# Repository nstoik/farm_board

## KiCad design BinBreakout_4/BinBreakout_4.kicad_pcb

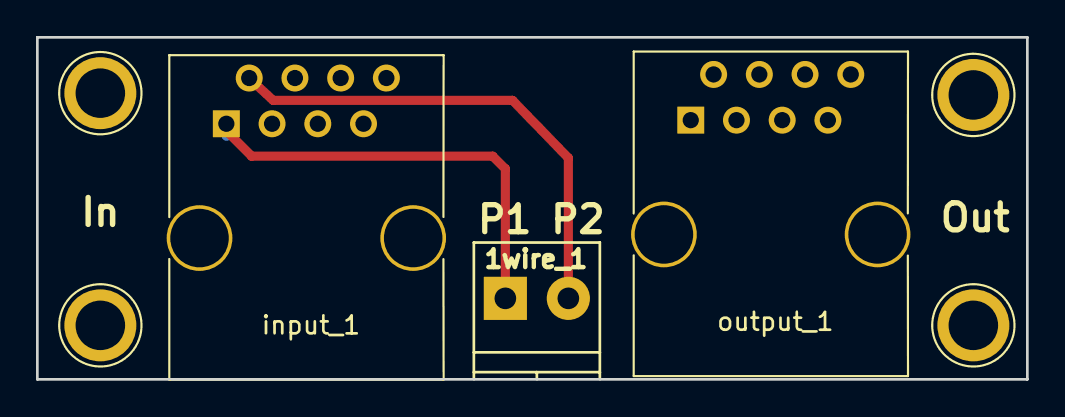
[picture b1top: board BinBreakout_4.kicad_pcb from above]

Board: 2 copper layers, 55.0 x 19.0 mm, 3 parts (0 on the bottom side), 2 nets.

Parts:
1wire_1: Screw_Terminal_01x02; TerminalBlock_Phoenix_PT-3.5mm_2pol
input_1: RJ45; RJ45_8
output_1: RJ45_8

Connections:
/pin_1: 1wire_1.1, input_1.1
/pin_2: 1wire_1.2, input_1.2

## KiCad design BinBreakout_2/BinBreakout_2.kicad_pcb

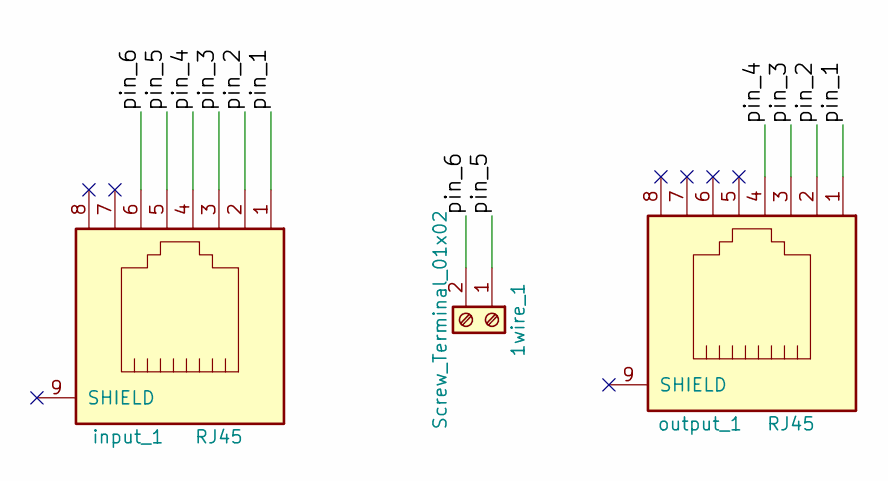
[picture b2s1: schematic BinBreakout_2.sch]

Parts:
1wire_1: Screw_Terminal_01x02; TerminalBlock_Phoenix_PT-3.5mm_2pol
input_1: RJ45; RJ45_8
output_1: RJ45; RJ45_8

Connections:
/pin_1: input_1.1, output_1.1
/pin_2: input_1.2, output_1.2
/pin_3: input_1.3, output_1.3
/pin_4: input_1.4, output_1.4
/pin_5: 1wire_1.1, input_1.5
/pin_6: 1wire_1.2, input_1.6

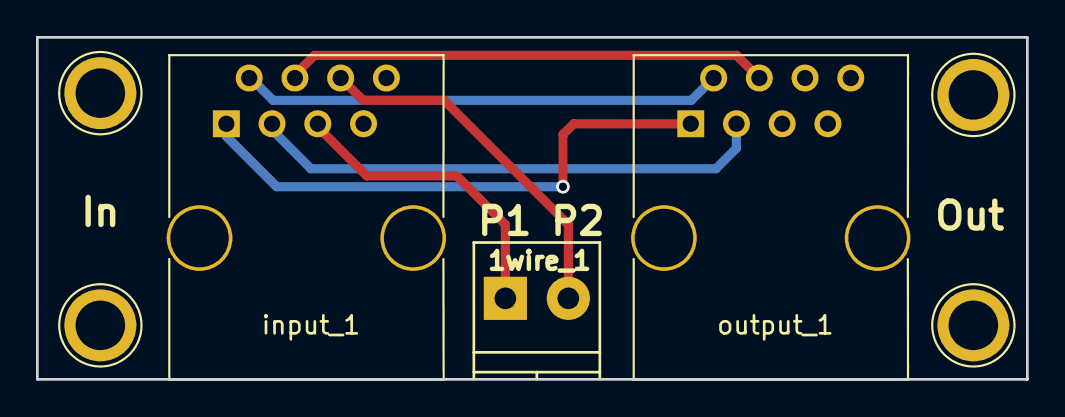
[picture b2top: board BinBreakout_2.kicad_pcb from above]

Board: 2 copper layers, 55.0 x 19.0 mm, 3 parts (0 on the bottom side), 6 nets.

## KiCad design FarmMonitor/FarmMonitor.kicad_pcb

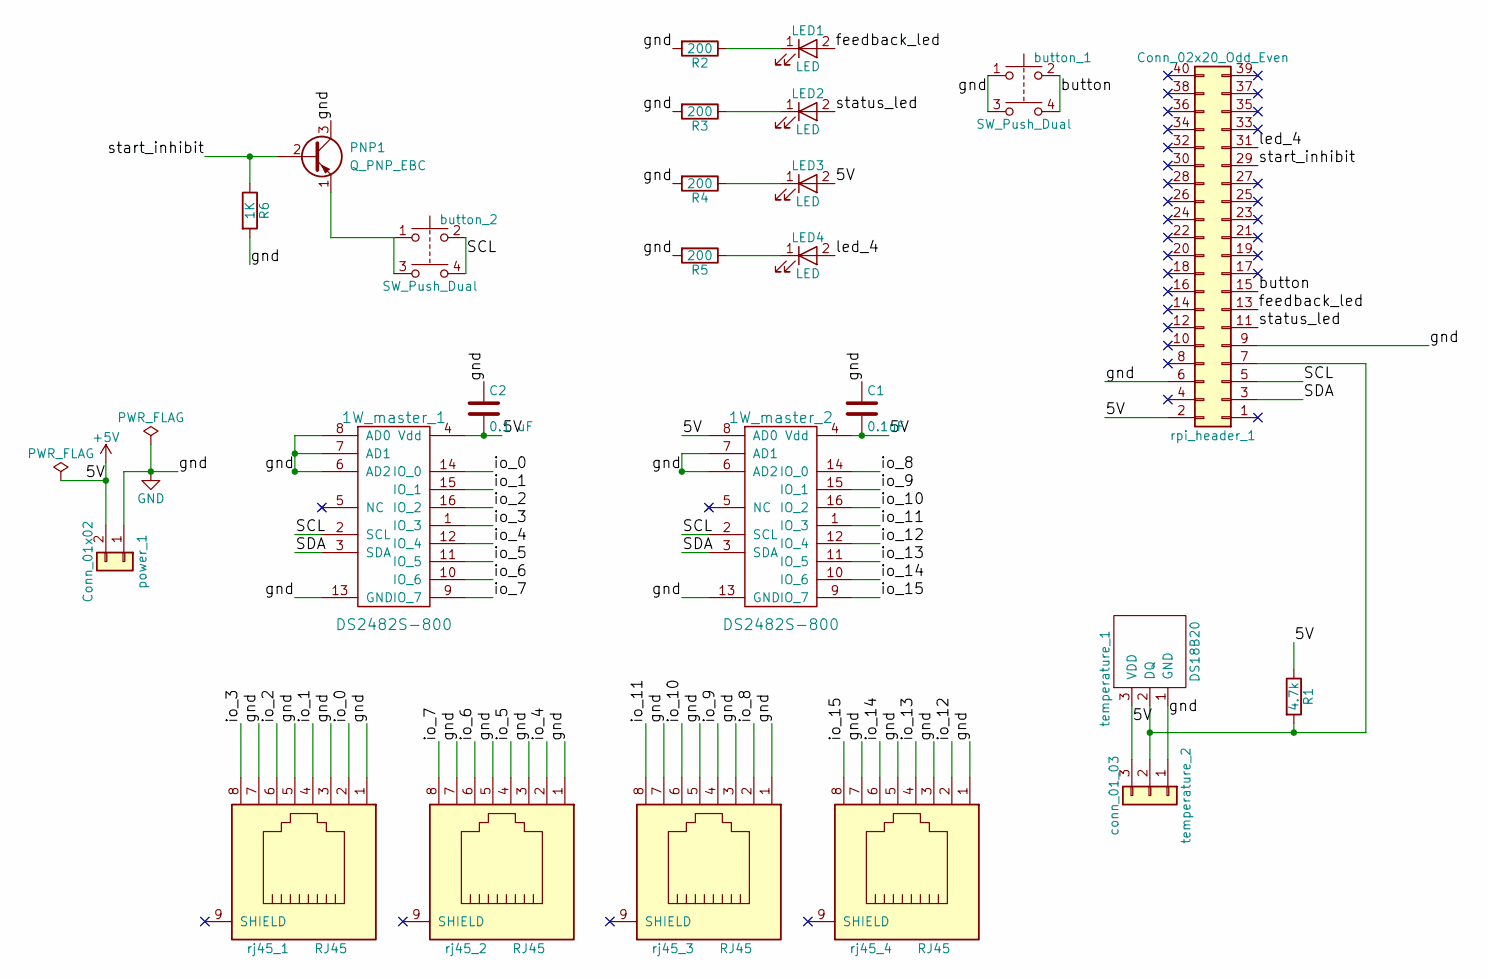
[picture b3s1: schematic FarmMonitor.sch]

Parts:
1W_master_1, 1W_master_2: DS2482S-800; SO-16-N
C1: 0.1uF; C_0805_HandSoldering
C2: 0.1 uF; C_0805_HandSoldering
LED1, LED2, LED3, LED4: LED; LED_D5.0mm
PNP1: Q_PNP_EBC; TO-92_Inline_Narrow_Oval
R1: 4.7k; R_0805_HandSoldering
R2, R3, R4, R5: 200; R_0805_HandSoldering
R6: 1K; R_0805_HandSoldering
button_1, button_2: SW_Push_Dual; Push_E-Switch_KS01Q01
power_1: Conn_01x02; TerminalBlock_Phoenix_PT-3.5mm_2pol
rj45_1, rj45_2, rj45_3, rj45_4: RJ45; RJ45_8
rpi_header_1: Conn_02x20_Odd_Even; Socket_Strip_Straight_2x20_Pitch2.54mm
temperature_1: DS18B20; TO-92_Horizontal2_Inline_Narrow_Oval
temperature_2: conn_01_03; TerminalBlock_Phoenix_MPT-2.54mm_3pol

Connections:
+5V: 1W_master_1.4 (Vdd), 1W_master_2.4 (Vdd), 1W_master_2.8 (AD0), C1.2, C2.2, LED3.2 (A), R1.1, power_1.2, rpi_header_1.2, temperature_1.3 (VDD), temperature_2.3
/SCL: 1W_master_1.2 (SCL), 1W_master_2.2 (SCL), button_2.2, button_2.4, rpi_header_1.5
/SDA: 1W_master_1.3 (SDA), 1W_master_2.3 (SDA), rpi_header_1.3
/button: button_1.2, button_1.4, rpi_header_1.15
/feedback_led: LED1.2 (A), rpi_header_1.13
/io_0: 1W_master_1.14 (IO_0), rj45_1.2
/io_1: 1W_master_1.15 (IO_1), rj45_1.4
/io_2: 1W_master_1.16 (IO_2), rj45_1.6
/io_3: 1W_master_1.1 (IO_3), rj45_1.8
/io_4: 1W_master_1.12 (IO_4), rj45_2.2
/io_5: 1W_master_1.11 (IO_5), rj45_2.4
/io_6: 1W_master_1.10 (IO_6), rj45_2.6
/io_7: 1W_master_1.9 (IO_7), rj45_2.8
/io_8: 1W_master_2.14 (IO_0), rj45_3.2
/io_9: 1W_master_2.15 (IO_1), rj45_3.4
/io_10: 1W_master_2.16 (IO_2), rj45_3.6
/io_11: 1W_master_2.1 (IO_3), rj45_3.8
/io_12: 1W_master_2.12 (IO_4), rj45_4.2
/io_13: 1W_master_2.11 (IO_5), rj45_4.4
/io_14: 1W_master_2.10 (IO_6), rj45_4.6
/io_15: 1W_master_2.9 (IO_7), rj45_4.8
/led_4: LED4.2 (A), rpi_header_1.31
/start_inhibit: PNP1.2 (B), R6.1, rpi_header_1.29
/status_led: LED2.2 (A), rpi_header_1.11
GND: 1W_master_1.6 (AD2), 1W_master_1.7 (AD1), 1W_master_1.8 (AD0), 1W_master_1.13 (GND), 1W_master_2.6 (AD2), 1W_master_2.7 (AD1), 1W_master_2.13 (GND), C1.1, C2.1, PNP1.3 (C), R2.2, R3.2, R4.2, R5.2, R6.2, button_1.1, button_1.3, power_1.1, rj45_1.1, rj45_1.3, rj45_1.5, rj45_1.7, rj45_2.1, rj45_2.3, rj45_2.5, rj45_2.7, rj45_3.1, rj45_3.3, rj45_3.5, rj45_3.7, rj45_4.1, rj45_4.3, rj45_4.5, rj45_4.7, rpi_header_1.6, rpi_header_1.9, temperature_1.1 (GND), temperature_2.1
unnamed: LED1.1 (K), R2.1
unnamed: LED2.1 (K), R3.1
unnamed: LED3.1 (K), R4.1
unnamed: LED4.1 (K), R5.1
unnamed: PNP1.1 (E), button_2.1, button_2.3
unnamed: R1.2, rpi_header_1.7, temperature_1.2 (DQ), temperature_2.2

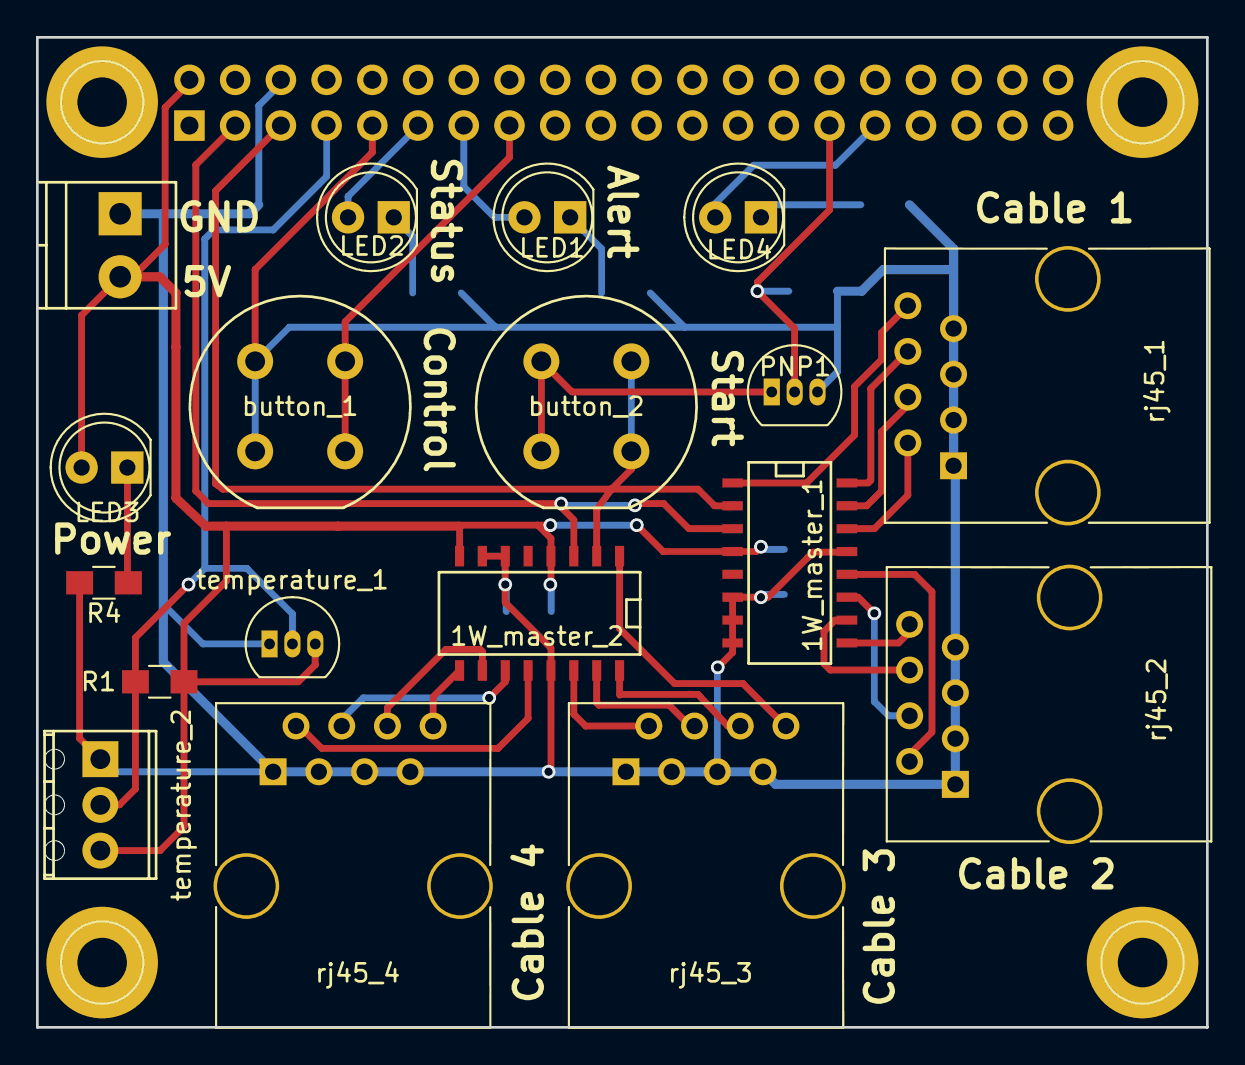
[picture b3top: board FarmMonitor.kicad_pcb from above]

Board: 2 copper layers, 65.0 x 55.0 mm, 25 parts (0 on the bottom side), 31 nets.

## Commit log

2017-11-27 :space_invader: Added .gitattributes & .gitignore files
2017-11-27 initial commit
    initial commit of 5 boards made in KiCad for farm monitor
2017-11-27 add png of boards
2017-12-01 version 1 of the boards. getting printed PCBs from OSH park
